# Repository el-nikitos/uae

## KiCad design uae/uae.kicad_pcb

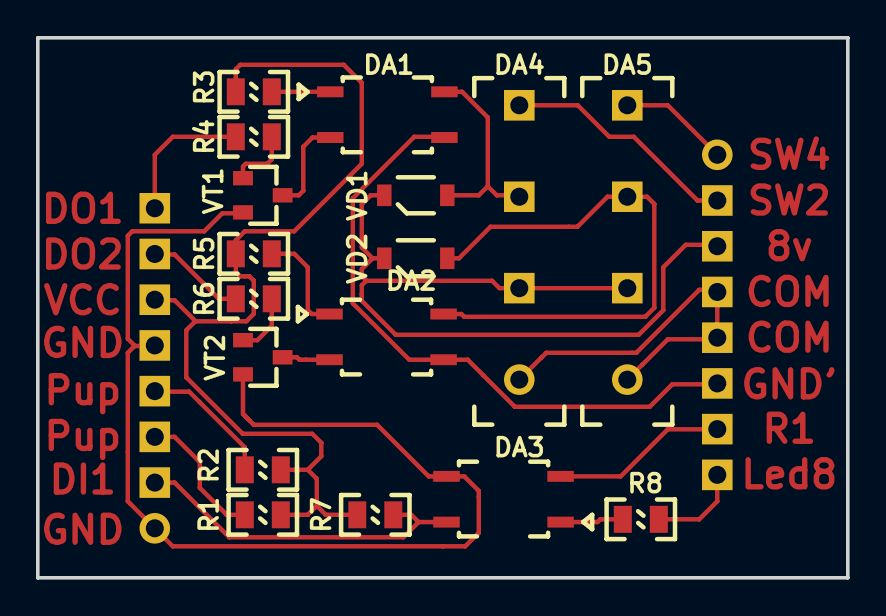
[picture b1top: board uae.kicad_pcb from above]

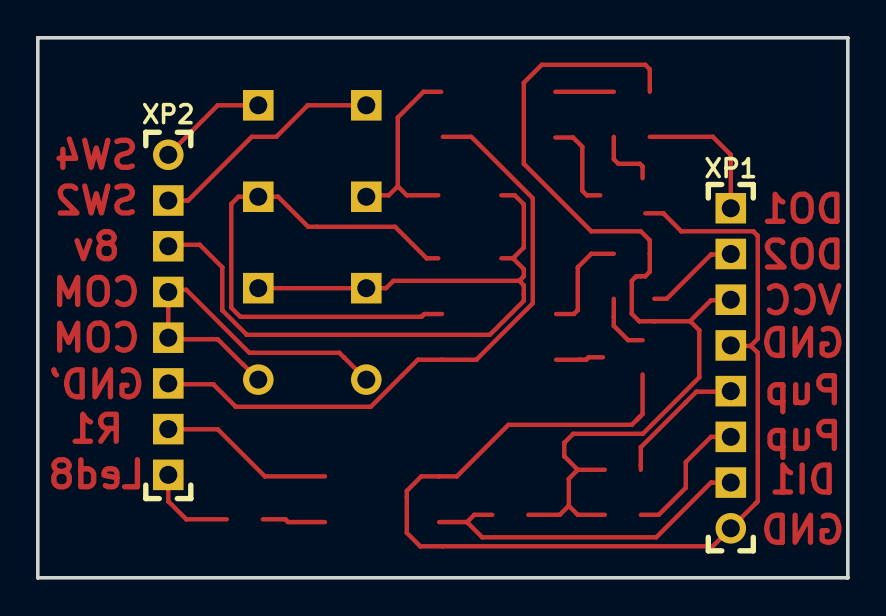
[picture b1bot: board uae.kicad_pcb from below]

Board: 2 copper layers, 45.0 x 30.0 mm, 19 parts (2 on the bottom side), 23 nets.

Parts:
DA1, DA2, DA3: LTV817S; SOP-4
DA4, DA5: EDR101A0500(SIP); реле_EDR101A0500(SIP7)
R1, R2, R4, R6, R7: 4,7k_0,125Вт_0805; Резистор_SMD_0805_0,125Вт
R3, R5: 47_0,125Вт_0805; Резистор_SMD_0805_0,125Вт
R8: 130_0,125Вт_0805; Резистор_SMD_0805_0,125Вт
VD1, VD2: S13_SOD-123; Диод_S13_SOD-123
VT1, VT2: Транзистор_NPN_BC817-16.215; Транзистор_IRLML6344TR_SOT-23
XP1, XP2: Вилка_PLS8; Вилка_PLS8_вертикальная

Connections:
/5V_OUT: DA4.3, DA5.3, VD1.2, VD2.2, XP2.3
/COM_OUT: DA4.1, DA5.1, XP2.4, XP2.5
/DI_1_RPI: DA3.4, R7.1, XP1.2
/DI_1_in: R8.2, XP2.8
/DI_gnd: DA3.2, XP2.7
/DO_1_RPI: R4.1, XP1.8
/DO_2_RPI: R6.1, XP1.7
/GND_OUT: DA1.3, DA2.3, XP2.6
/GND_RPI: DA3.3, VT1.2, VT2.2, XP1.1, XP1.5
/OUT_1: DA4.7, XP2.2
/OUT_2: DA5.7, XP2.1
/PULL_UP_1: R1.1, XP1.3
/PULL_UP_2: R2.1, XP1.4
/VCC_RPI: R1.2, R2.2, R3.1, R5.1, R7.2, XP1.6
unnamed: DA1.1, R3.2
unnamed: DA1.2, VT1.3
unnamed: DA1.4, DA4.5, VD1.1
unnamed: DA2.1, R5.2
unnamed: DA2.2, VT2.3
unnamed: DA2.4, DA5.5, VD2.1
unnamed: DA3.1, R8.1
unnamed: R4.2, VT1.1
unnamed: R6.2, VT2.1

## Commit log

2019-04-01 на рабочем поле размещены компоненты и закреплены посадочные места
2019-04-01 первая неподтвержденная версия
2019-04-02 уменьшен зазор паяльной маски, заменены герберы
2019-04-02 020419
